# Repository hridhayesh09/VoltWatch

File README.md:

Overview
VoltWatch is a custom-designed PCB system that monitors residential power quality in real time, detects voltage surges, and sends alerts before equipment damage occurs. Inspired by a personal experience where a thunderstorm surge destroyed a pair of speakers.

## Hardware
- ESP32 WROOM-32 microcontroller
- ZMPT101B AC voltage sensor
- Custom PCB designed and routed in KiCad, with Gerber and drill files in hardware/

## Stack
- Firmware: Embedded C on ESP32 (PlatformIO)
- Backend: Python Flask + SQLite
- Alerts: Twilio SMS (coming soon)
- Dashboard: React (coming soon)
- ML: scikit-learn anomaly detection (coming soon)

## How It Works
The ESP32 reads voltage data from the ZMPT101B sensor 1000 times per second, calculates peak-to-peak values, detects surge events, and sends timestamped data to a Flask backend over WiFi for storage and analysis.

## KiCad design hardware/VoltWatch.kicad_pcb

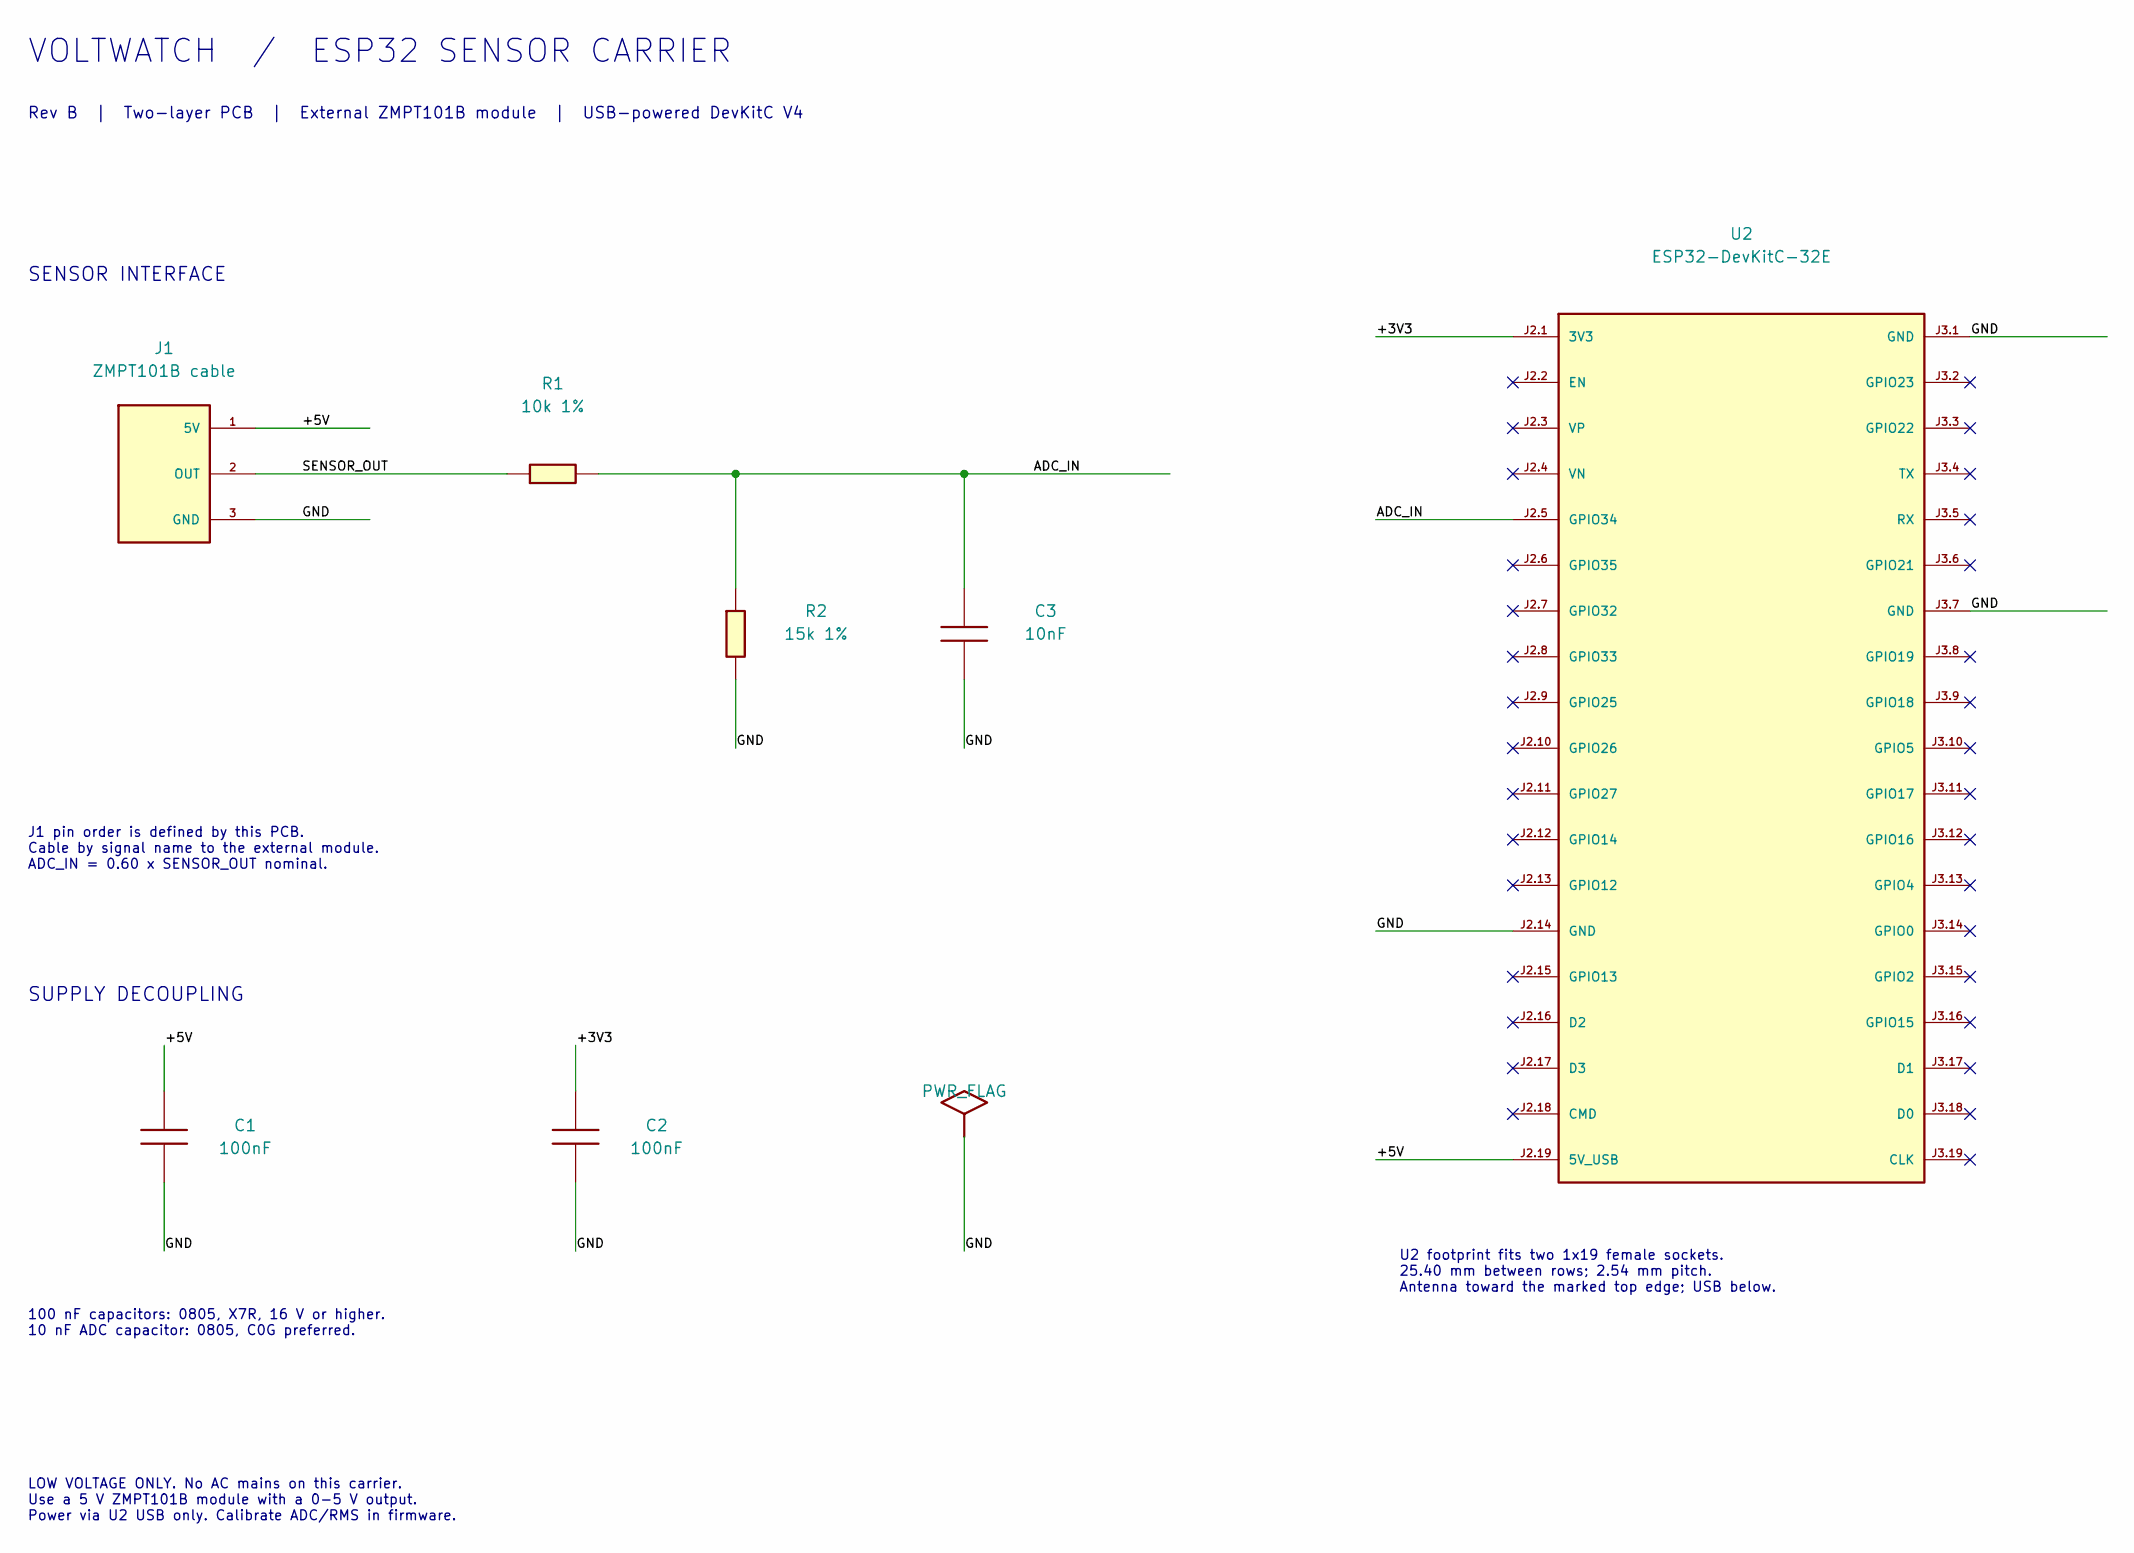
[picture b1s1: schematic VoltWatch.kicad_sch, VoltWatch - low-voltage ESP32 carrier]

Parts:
C1, C2: 100nF; C_0805_2012Metric
C3: 10nF; C_0805_2012Metric
J1: ZMPT101B cable; PinHeader_1x03_P2.54mm_Vertical
R1: 10k 1%; R_0805_2012Metric
R2: 15k 1%; R_0805_2012Metric
U2: ESP32-DevKitC-32E; ESP32_DevKitC_V4_Sockets

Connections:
/+3V3: C2.1, U2.J2.1 (3V3)
/+5V: C1.1, J1.1 (5V), U2.J2.19 (5V_USB)
/ADC_IN: C3.1, R1.2, R2.1, U2.J2.5 (GPIO34)
/GND: C1.2, C2.2, C3.2, J1.3 (GND), R2.2, U2.J2.14 (GND), U2.J3.1 (GND), U2.J3.7 (GND)
/SENSOR_OUT: J1.2 (OUT), R1.1

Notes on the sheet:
VOLTWATCH / ESP32 SENSOR CARRIER
Rev B | Two-layer PCB | External ZMPT101B module | USB-powered DevKitC V4
SENSOR INTERFACE
J1 pin order is defined by this PCB. Cable by signal name to the external module. ADC_IN = 0.60 x SENSOR_OUT nominal.
SUPPLY DECOUPLING
100 nF capacitors: 0805, X7R, 16 V or higher. 10 nF ADC capacitor: 0805, C0G preferred.
U2 footprint fits two 1x19 female sockets. 25.40 mm between rows; 2.54 mm pitch. Antenna toward the marked top edge; USB below.
LOW VOLTAGE ONLY. No AC mains on this carrier. Use a 5 V ZMPT101B module with a 0-5 V output. Power via U2 USB only. Calibrate ADC/RMS in firmware.

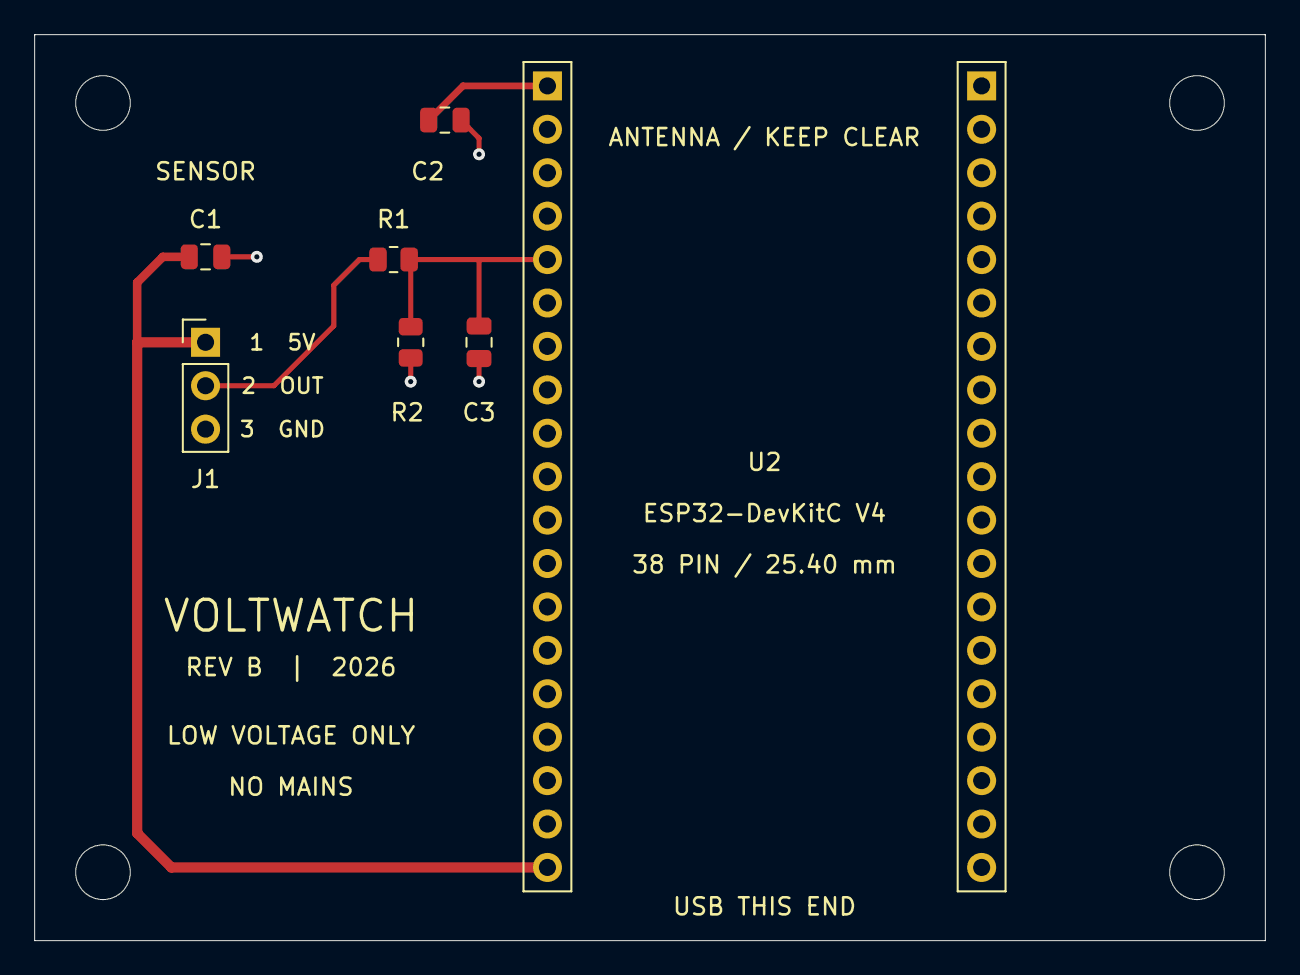
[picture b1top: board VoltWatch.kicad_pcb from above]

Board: 2 copper layers, 72.0 x 53.0 mm, 11 parts (0 on the bottom side), 5 nets.

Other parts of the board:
H1, H2, H3, H4: M3; MountingHole_3.2mm_M3
